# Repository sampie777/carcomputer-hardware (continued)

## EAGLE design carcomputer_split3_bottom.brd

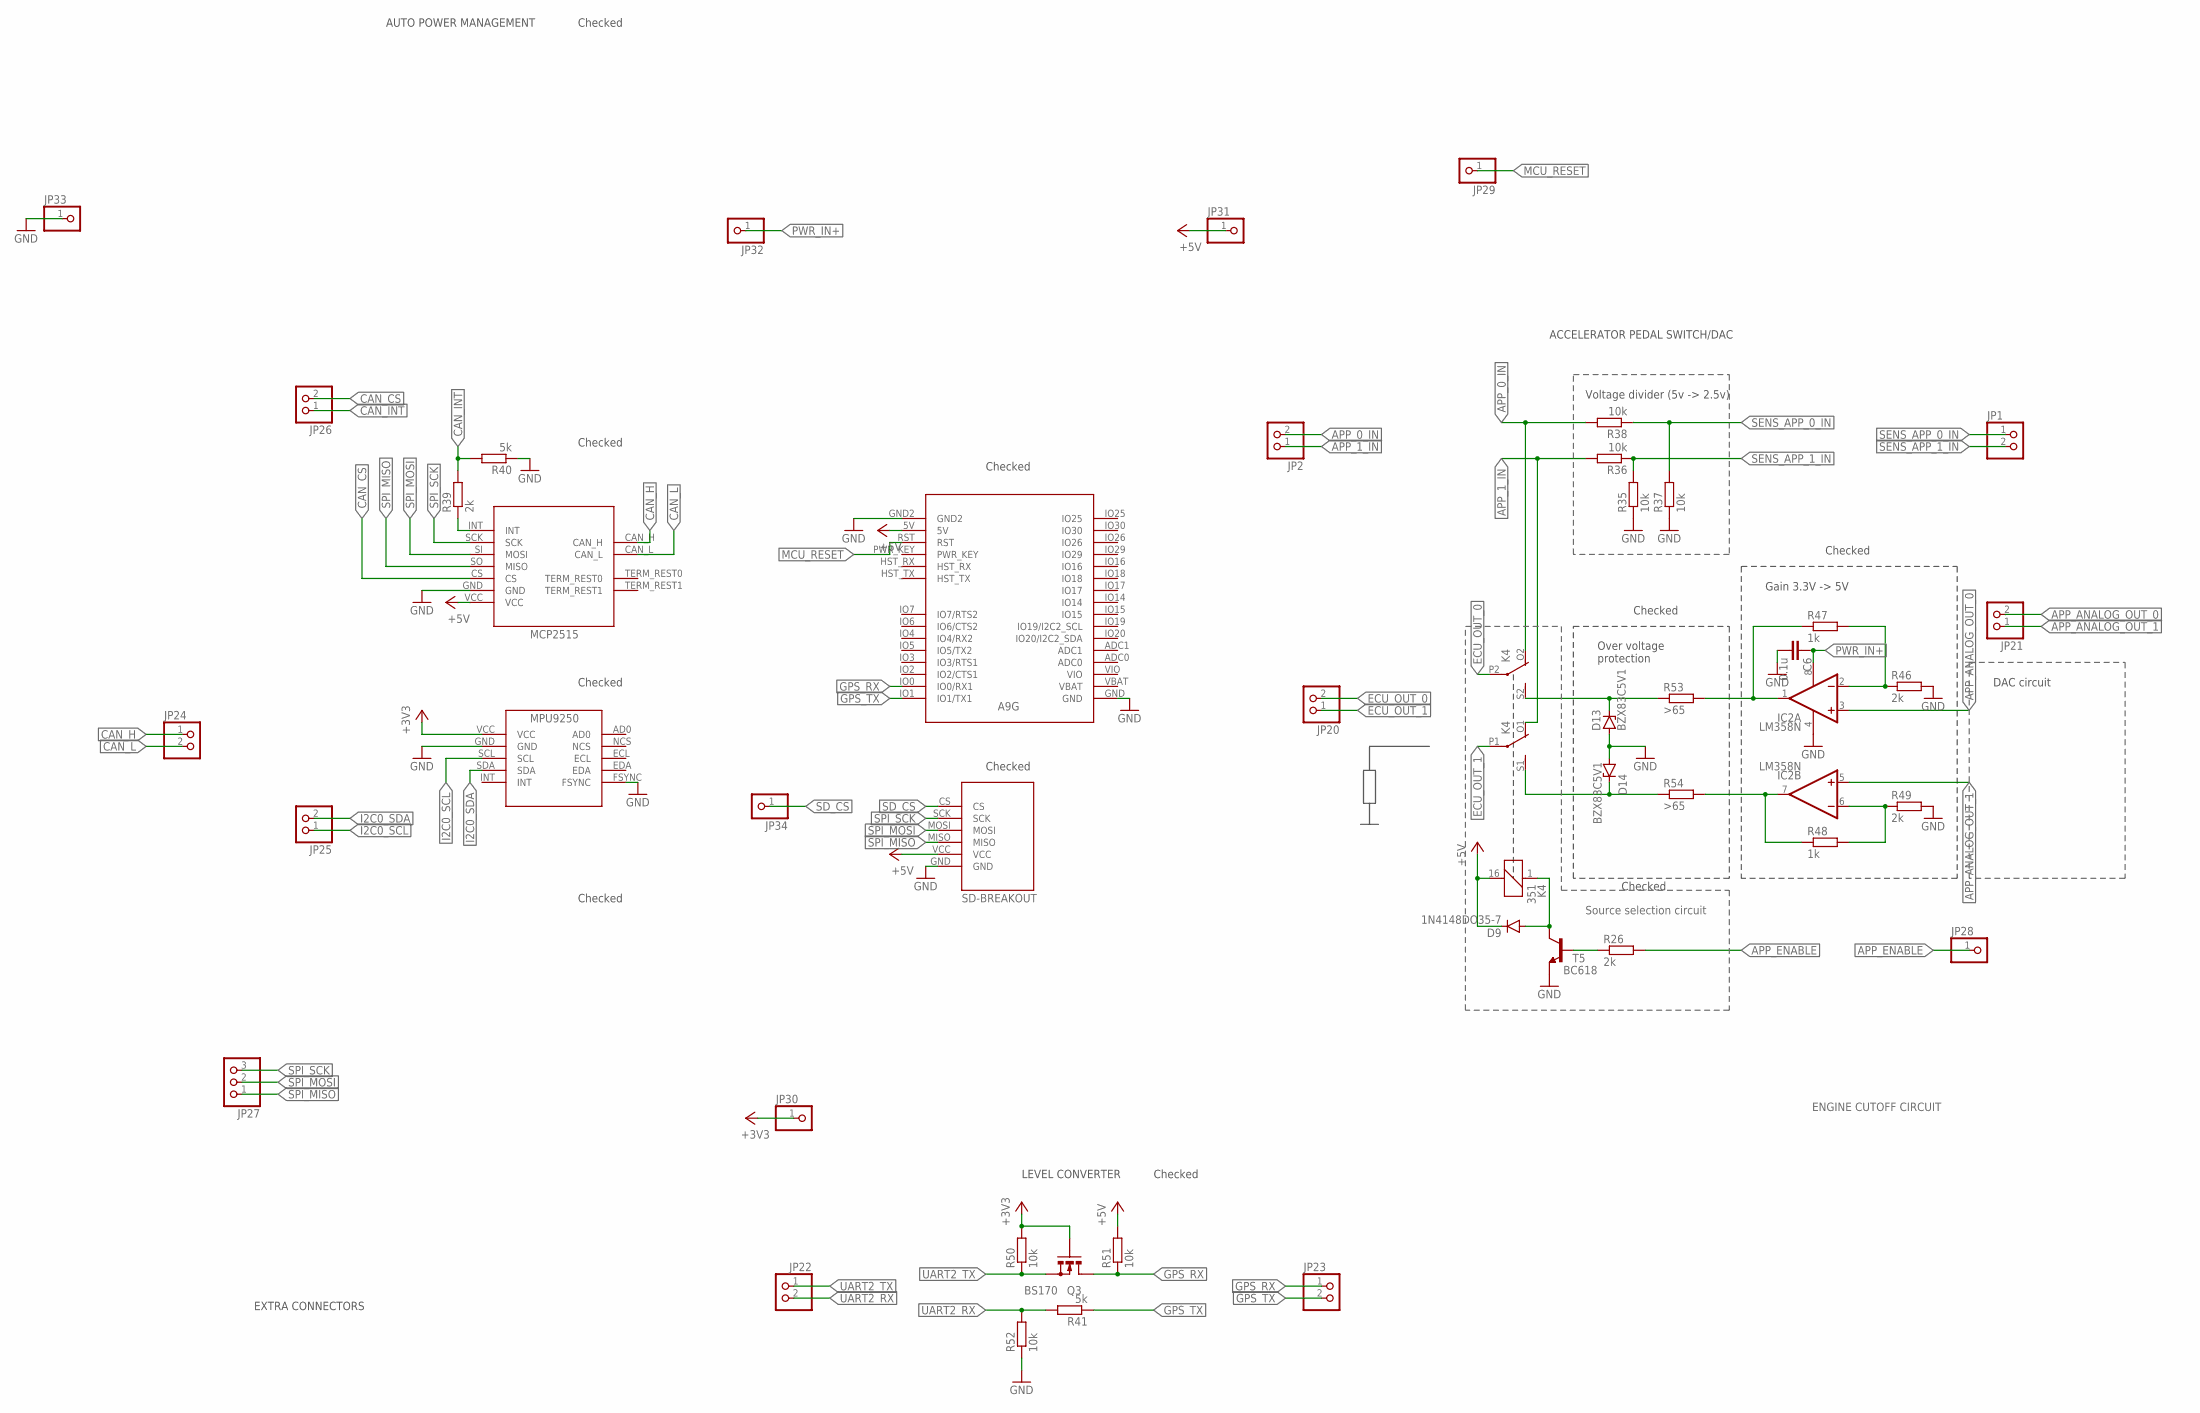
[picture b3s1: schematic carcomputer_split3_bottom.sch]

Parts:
C6: 0.1u; C025-050X050
D9: 1N4148DO35-7; DO35-7
D13, D14: BZX83C5V1; DO41Z10
IC2: LM358N; DIL08
JP1, JP2, JP20, JP21, JP22, JP23, JP24, JP25, JP26: PINHD-1X2; 1X02
JP27: PINHD-1X3; 1X03
JP28, JP29, JP30, JP31, JP32, JP33, JP34: PINHD-1X1; 1X01
K4: 351
Q3: BS170; SOT54E
R26, R39, R46, R49: 2k; 0207/7
R35, R36, R37, R38, R50, R51, R52: 10k; 0207/7
R40, R41: 5k; 0207/7
R47, R48: 1k; 0207/7
R53, R54: >65; 0207/7
T5: BC618; TO92-EBC
U$8: MCP2515_DEVBOARDINVERTED; MCP2515_DEVBOARD_INVERTED
U$9: MPU9250_BREAKOUT
U$11: HKD-MICRO-SD-BREAKOUT
U$12: A9G

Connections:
+3V3: JP30.1, Q3.G, R50.2, U$9.VCC
+5V: D9.C, JP31.1, K4.16 (2), R51.2, U$8.VCC, U$11.VCC, U$12.5V
APP_0_IN: JP2.2, K4.O2 (O), R38.2
APP_1_IN: JP2.1, K4.O1 (O), R36.2
APP_ANALOG_OUT_0: IC2.3 (+IN), JP21.2
APP_ANALOG_OUT_1: IC2.5 (+IN), JP21.1
APP_ENABLE: JP28.1, R26.2
CAN_CS: JP26.2, U$8.CS
CAN_H: JP24.1, U$8.CAN_H
CAN_INT: JP26.1, R39.2, R40.2
CAN_L: JP24.2, U$8.CAN_L
ECU_OUT_0: JP20.2, K4.P2
ECU_OUT_1: JP20.1, K4.P1
GND: C6.2, D13.A, D14.A, IC2.4 (V-), JP33.1, R35.1, R37.1, R40.1, R46.2, R49.2, R52.1, T5.E, U$8.GND, U$9.FSYNC, U$9.GND, U$11.GND, U$12.GND, U$12.GND2
GPS_RX: JP23.1, Q3.D, R51.1, U$12.IO0 (IO0/RX1)
GPS_TX: JP23.2, R41.1, U$12.IO1 (IO1/TX1)
I2C0_SCL: JP25.1, U$9.SCL
I2C0_SDA: JP25.2, U$9.SDA
MCU_RESET: JP29.1, U$12.RST
unnamed: D9.A, K4.1, T5.C
unnamed: R26.1, T5.B
unnamed: D14.C, K4.S1 (S), R54.1
unnamed: IC2.1 (OUT), R47.1, R53.2
unnamed: R39.1, U$8.INT
unnamed: IC2.2 (-IN), R46.1, R47.2
unnamed: IC2.6 (-IN), R48.2, R49.1
unnamed: D13.C, K4.S2 (S), R53.1
unnamed: IC2.7 (OUT), R48.1, R54.2
PWR_IN+: C6.1, IC2.8 (V+), JP32.1
SD_CS: JP34.1, U$11.CS
SENS_APP_0_IN: JP1.1, R37.2, R38.1
SENS_APP_1_IN: JP1.2, R35.2, R36.1
SPI_MISO: JP27.1, U$8.SO (MISO), U$11.MISO
SPI_MOSI: JP27.2, U$8.SI (MOSI), U$11.MOSI
SPI_SCK: JP27.3, U$8.SCK, U$11.SCK
UART2_RX: JP22.2, R41.2, R52.2
UART2_TX: JP22.1, Q3.S, R50.1

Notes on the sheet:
Voltage divider (5v -> 2.5v)
DAC circuit
Source selection circuit
AUTO POWER MANAGEMENT
ACCELERATOR PEDAL SWITCH/DAC
EXTRA CONNECTORS
Gain 3.3V -> 5V
Over voltage protection
Checked
LEVEL CONVERTER
ENGINE CUTOFF CIRCUIT

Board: 2 copper layers, 46 parts (0 on the bottom side), 37 nets, no tracks yet.

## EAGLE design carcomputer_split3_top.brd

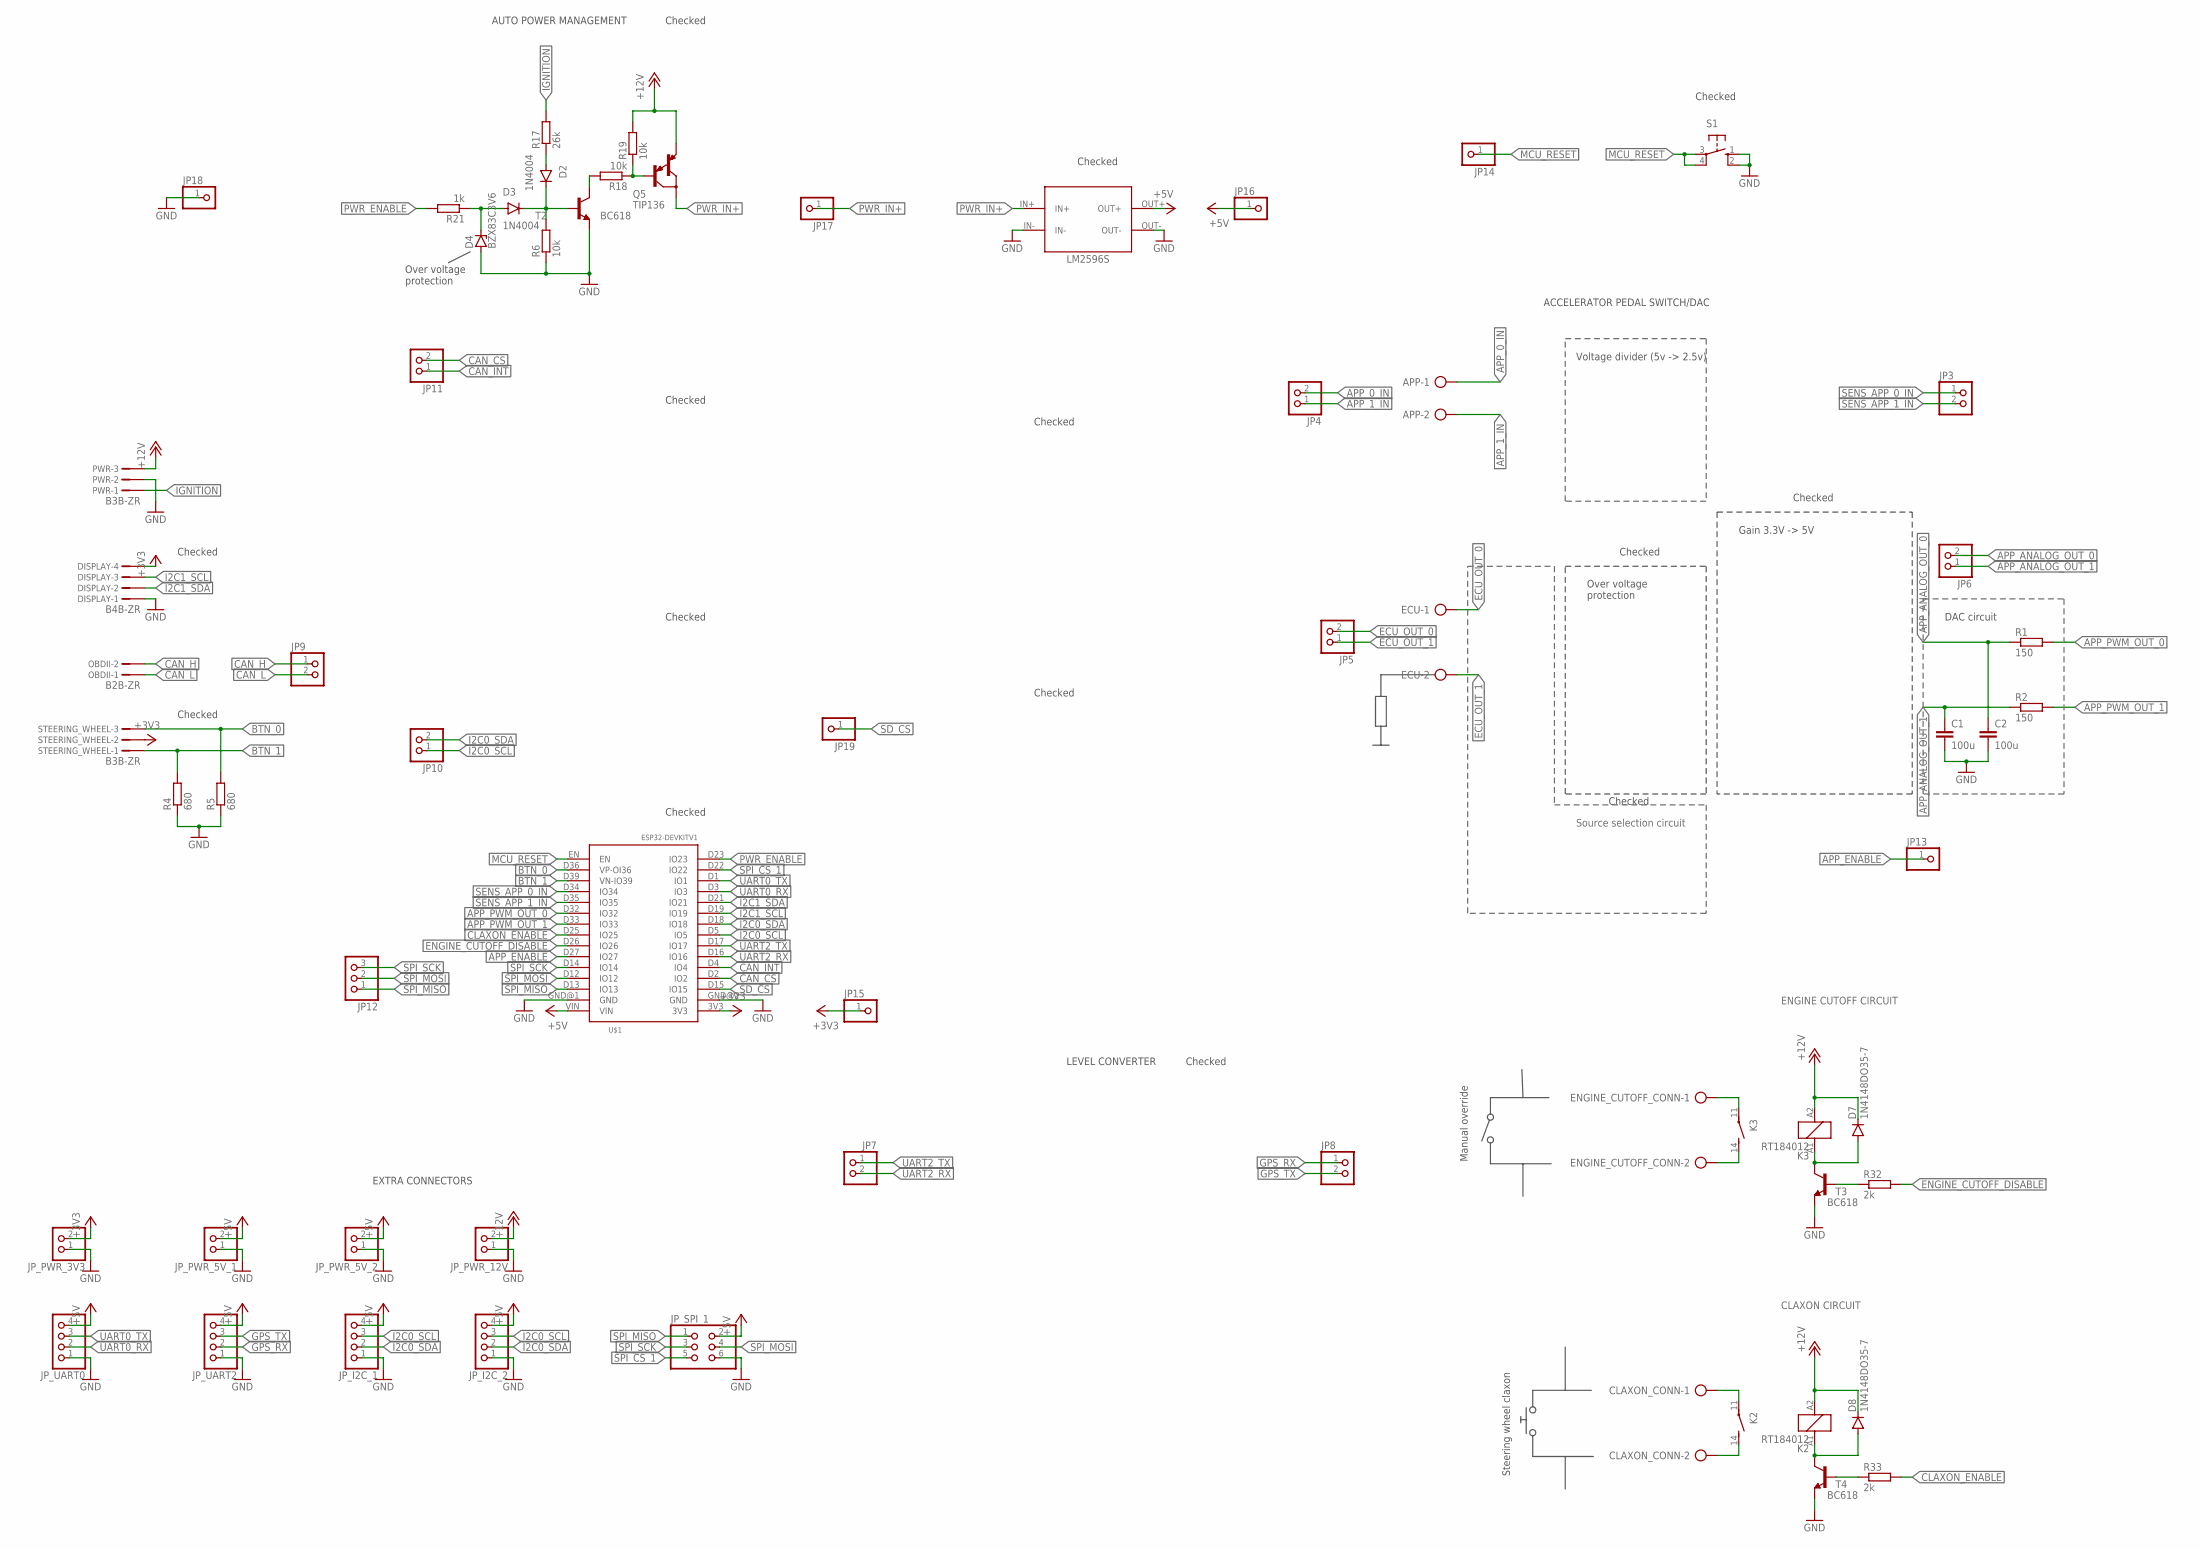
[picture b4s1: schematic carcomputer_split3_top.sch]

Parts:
APP: AK300/2
C1, C2: 100u; C025-050X050
CLAXON_CONN: AK300/2
D2, D3: 1N4004; DO41-10
D4: BZX83C3V6; DO41Z10
D7, D8: 1N4148DO35-7; DO35-7
DISPLAY: B4B-ZR
ECU: AK300/2
ENGINE_CUTOFF_CONN: AK300/2
JP3, JP4, JP5, JP6, JP7, JP8, JP9, JP10, JP11: PINHD-1X2; 1X02
JP12: PINHD-1X3; 1X03
JP13, JP14, JP15, JP16, JP17, JP18, JP19: PINHD-1X1; 1X01
JP_I2C_1, JP_I2C_2: PINHD-1X4; 1X04
JP_PWR_3V3, JP_PWR_5V_1, JP_PWR_5V_2, JP_PWR_12V: PINHD-1X2; 1X02
JP_SPI_1: PINHD-2X3; 2X03
JP_UART0, JP_UART2: PINHD-1X4; 1X04
K2, K3: RT184012; RT-N/O12A3.5
OBDII: B2B-ZR
PWR: B3B-ZR
Q5: TIP136; TO220
R1, R2: 150; 0207/7
R4, R5: 680; 0207/7
R6, R18, R19: 10k; 0207/7
R17: 26k; 0207/7
R21: 1k; 0207/7
R32, R33: 2k; 0207/7
S1: 10-XX; B3F-10XX
STEERING_WHEEL: B3B-ZR
T2, T3, T4: BC618; TO92-EBC
U$1: ESP32DEVKITV1; ESP32-DEVKITV1
U$4: LM2596S

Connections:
+3V3: DISPLAY.4, JP15.1, JP_PWR_3V3.2, STEERING_WHEEL.2, U$1.3V3
+5V: JP16.1, JP_I2C_1.4, JP_I2C_2.4, JP_PWR_5V_1.2, JP_PWR_5V_2.2, JP_SPI_1.2, JP_UART0.4, JP_UART2.4, U$1.VIN, U$4.OUT+
+12V: D7.C, D8.C, JP_PWR_12V.2, K2.A2 (2), K3.A2 (2), PWR.3, Q5.3 (E), R19.2
APP_0_IN: APP.1, JP4.2
APP_1_IN: APP.2, JP4.1
APP_ANALOG_OUT_0: C2.1, JP6.2, R1.1
APP_ANALOG_OUT_1: C1.1, JP6.1, R2.1
APP_ENABLE: JP13.1, U$1.D27 (IO27)
APP_PWM_OUT_0: R1.2, U$1.D32 (IO32)
APP_PWM_OUT_1: R2.2, U$1.D33 (IO33)
BTN_0: R5.2, STEERING_WHEEL.3, U$1.D36 (VP-OI36)
BTN_1: R4.2, STEERING_WHEEL.1, U$1.D39 (VN-IO39)
CAN_CS: JP11.2, U$1.D2 (IO2)
CAN_H: JP9.1, OBDII.2
CAN_INT: JP11.1, U$1.D4 (IO4)
CAN_L: JP9.2, OBDII.1
CLAXON_ENABLE: R33.2, U$1.D25 (IO25)
ECU_OUT_0: ECU.1, JP5.2
ECU_OUT_1: ECU.2, JP5.1
ENGINE_CUTOFF_DISABLE: R32.2, U$1.D26 (IO26)
GND: C1.2, C2.2, D4.A, DISPLAY.1, JP18.1, JP_I2C_1.1, JP_I2C_2.1, JP_PWR_3V3.1, JP_PWR_5V_1.1, JP_PWR_5V_2.1, JP_PWR_12V.1, JP_SPI_1.6, JP_UART0.1, JP_UART2.1, PWR.2, R4.1, R5.1, R6.1, S1.1 (S), S1.2 (S1), T2.E, T3.E, T4.E, U$1.GND@1 (GND), U$1.GND@2 (GND), U$4.IN-, U$4.OUT-
GPS_RX: JP8.1, JP_UART2.2
GPS_TX: JP8.2, JP_UART2.3
I2C0_SCL: JP10.1, JP_I2C_1.3, JP_I2C_2.3, U$1.D5 (IO5)
I2C0_SDA: JP10.2, JP_I2C_1.2, JP_I2C_2.2, U$1.D18 (IO18)
I2C1_SCL: DISPLAY.3, U$1.D19 (IO19)
I2C1_SDA: DISPLAY.2, U$1.D21 (IO21)
IGNITION: PWR.1, R17.2
MCU_RESET: JP14.1, S1.3, S1.4 (P1), U$1.EN
unnamed: D2.C, D3.C, R6.2, T2.B
unnamed: D3.A, D4.C, R21.1
unnamed: D2.A, R17.1
unnamed: Q5.1 (B), R18.1, R19.1
unnamed: R18.2, T2.C
unnamed: ENGINE_CUTOFF_CONN.1, K3.11
unnamed: ENGINE_CUTOFF_CONN.2, K3.14 (S)
unnamed: D7.A, K3.A1 (1), T3.C
unnamed: D8.A, K2.A1 (1), T4.C
unnamed: R33.1, T4.B
unnamed: R32.1, T3.B
unnamed: CLAXON_CONN.1, K2.11
unnamed: CLAXON_CONN.2, K2.14 (S)
PWR_ENABLE: R21.2, U$1.D23 (IO23)
PWR_IN+: JP17.1, Q5.2 (C), U$4.IN+
SD_CS: JP19.1, U$1.D15 (IO15)
SENS_APP_0_IN: JP3.1, U$1.D34 (IO34)
SENS_APP_1_IN: JP3.2, U$1.D35 (IO35)
SPI_CS_1: JP_SPI_1.5, U$1.D22 (IO22)
SPI_MISO: JP12.1, JP_SPI_1.1, U$1.D13 (IO13)
SPI_MOSI: JP12.2, JP_SPI_1.4, U$1.D12 (IO12)
SPI_SCK: JP12.3, JP_SPI_1.3, U$1.D14 (IO14)
UART0_RX: JP_UART0.2, U$1.D3 (IO3)
UART0_TX: JP_UART0.3, U$1.D1 (IO1)
UART2_RX: JP7.2, U$1.D16 (IO16)
UART2_TX: JP7.1, U$1.D17 (IO17)

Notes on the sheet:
Voltage divider (5v -> 2.5v)
DAC circuit
Source selection circuit
Over voltage protection
AUTO POWER MANAGEMENT
ACCELERATOR PEDAL SWITCH/DAC
EXTRA CONNECTORS
Gain 3.3V -> 5V
Checked
LEVEL CONVERTER
ENGINE CUTOFF CIRCUIT
Manual override
CLAXON CIRCUIT
Steering wheel claxon

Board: 2 copper layers, 61 parts (3 on the bottom side), 55 nets, no tracks yet.
